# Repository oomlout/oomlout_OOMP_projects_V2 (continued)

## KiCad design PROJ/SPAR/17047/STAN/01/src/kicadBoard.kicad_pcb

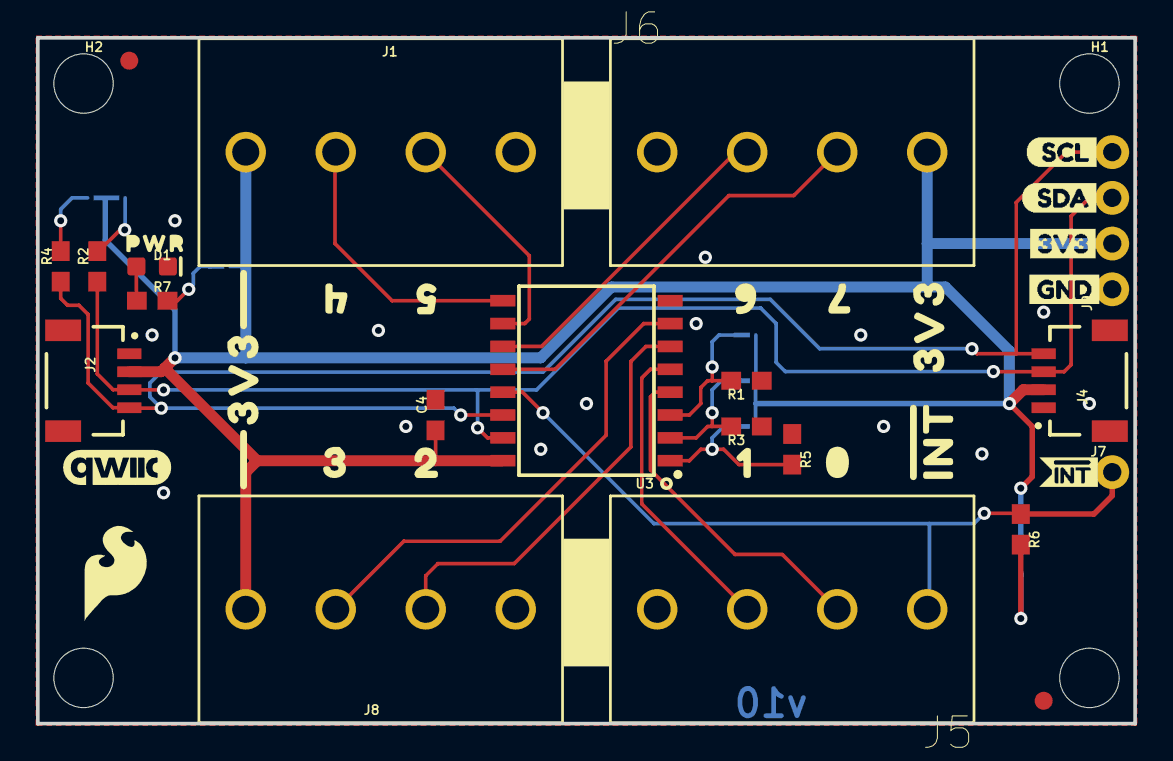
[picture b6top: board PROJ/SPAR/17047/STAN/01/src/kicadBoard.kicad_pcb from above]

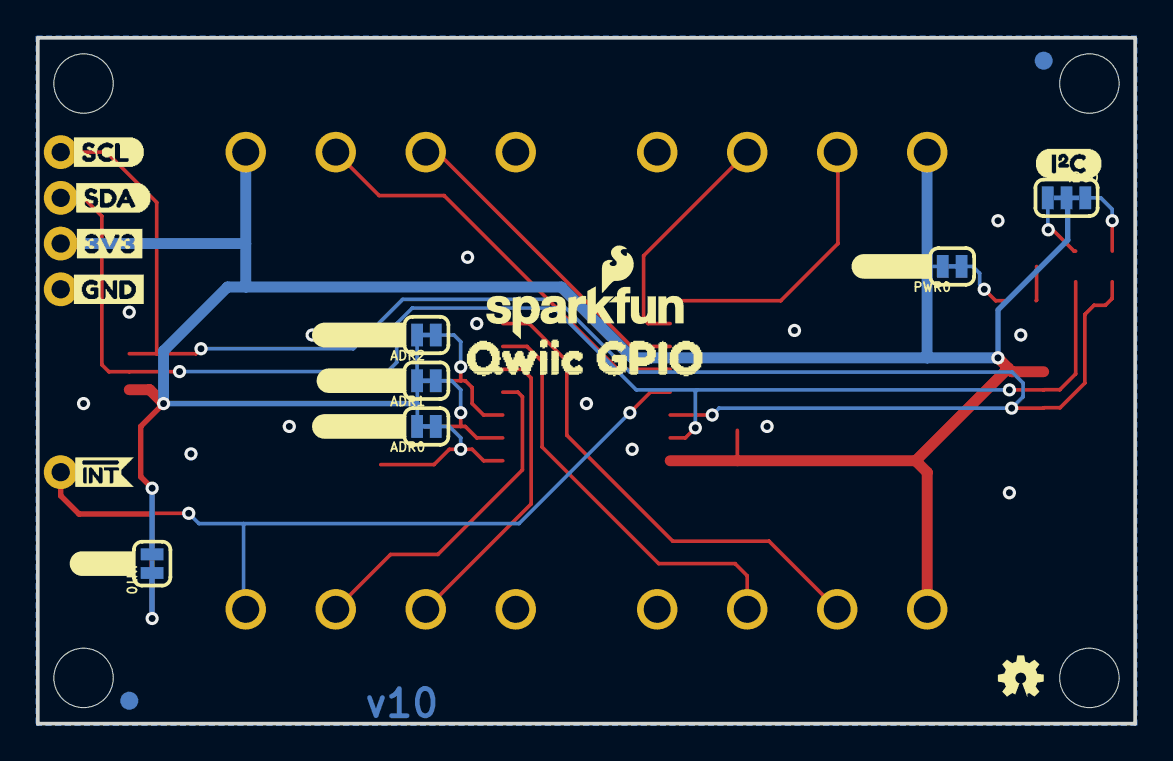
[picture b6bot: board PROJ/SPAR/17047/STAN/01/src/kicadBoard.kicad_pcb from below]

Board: 2 copper layers, 61.0 x 38.1 mm, 69 parts (22 on the bottom side), 21 nets.

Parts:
ADR0, ADR1, ADR2: JUMPER-SMT_2_NC_TRACE_SILK; SMT-JUMPER_2_NC_TRACE_SILK
C4: 0.1uF; 0603
D1: RED; LED-0603
FD1, FD2: FIDUCIAL1X2; FIDUCIAL-1X2
FRAME1: FRAME-LETTER; CREATIVE_COMMONS
H1, H2: STAND-OFF
I2C0: JUMPER-SMT_3_2-NC_TRACE_SILK; SMT-JUMPER_3_2-NC_TRACE_SILK
INT0: JUMPER-SMT_2_NC_TRACE_SILK; SMT-JUMPER_2_NC_TRACE_SILK
J1, J5, J6, J8: LATCHTERMINAL-5MM-4
J2, J4: QWIIC; JST04_1MM_RA
J7: 1X01_NO_SILK
J9: 1X04_NO_SILK
JP2, JP6: FIDUCIAL1X2; FIDUCIAL-1X2
JP3, JP4: STAND-OFF
LOGO1: OSHW-LOGOMINI; OSHW-LOGO-MINI
LOGO2: REVISION
LOGO3: SFE_LOGO_NAME_FLAME.1_INCH; SFE_LOGO_NAME_FLAME_.1
LOGO4: SFE_LOGO_FLAME.2_INCH; SFE_LOGO_FLAME_.2
PWR0: JUMPER-SMT_2_NC_TRACE_SILK; SMT-JUMPER_2_NC_TRACE_SILK
R1, R2, R3, R4, R5: 2.2k; 0603
R6: 10k; 0603
R7: 1k; 0603
U3: TCA9534; 16SOIC
U$1: I2C
U$2: 20
U$3, U$26: 3V33
U$4: 30
U$5: #ADR1#0
U$6: 10
U$7, U$25: GND4
U$8: QWIIC_GPIO7
U$9: SCL6
U$10: SDA5
U$11: #ADR2#0
U$12: #INT#0
U$13, U$22, U$29: #INT0
U$14: 00
U$15: #ADR0#0
U$21: QWIIC_6MM
U$23: SCL0
U$24: SDA1
U$30, U$31: 3V30
U$32: 40
U$33: 50
U$34: PWR0
U$35: 60
U$37: 70
U$38, U$40: #GND#0
U$39: #PWR#0

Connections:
3.3V: ADR0.2, ADR1.2, ADR2.2, C4.1, I2C0.2, INT0.2, J1.1, J2.2, J4.2, J6.4, J8.4, J9.2, PWR0.2, U3.16
ADR0: ADR0.1, R5.2, U3.1
ADR1: ADR1.1, R3.2, U3.2
ADR2: ADR2.1, R1.2, U3.3
GND: C4.2, D1.C, J1.4, J2.1, J4.1, J5.4, J6.1, J8.1, J9.1, R1.1, R3.1, R5.1, U3.8
unnamed: INT0.1, R6.2
unnamed: D1.A, R7.1
unnamed: PWR0.1, R7.2
P0: J5.2, U3.4
P1: J5.3, U3.5
P2: J8.2, U3.6
P3: J8.3, U3.7
P4: J1.2, U3.9
P5: J1.3, U3.10
P6: J6.2, U3.11
P7: J6.3, U3.12
SCL: J2.4, J4.4, J9.4, R4.1, U3.14
SCL_PU1: I2C0.1, R2.2
SDA: J2.3, J4.3, J9.3, R2.1, U3.15
SDA_PU1: I2C0.3, R4.2
~INT: J5.1, J7.1, R6.1, U3.13

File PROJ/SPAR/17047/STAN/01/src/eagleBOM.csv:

"Part";"Value";"Device";"Package";"Description";"DESIGNER";"PROD_ID";"REV";"STOREFRONT_SKU";"VALUE";
"ADR0";"JUMPER-SMT_2_NC_TRACE_SILK";"JUMPER-SMT_2_NC_TRACE_SILK";"SMT-JUMPER_2_NC_TRACE_SILK";"Normally closed trace jumper";"";"";"";"";"";
"ADR1";"JUMPER-SMT_2_NC_TRACE_SILK";"JUMPER-SMT_2_NC_TRACE_SILK";"SMT-JUMPER_2_NC_TRACE_SILK";"Normally closed trace jumper";"";"";"";"";"";
"ADR2";"JUMPER-SMT_2_NC_TRACE_SILK";"JUMPER-SMT_2_NC_TRACE_SILK";"SMT-JUMPER_2_NC_TRACE_SILK";"Normally closed trace jumper";"";"";"";"";"";
"C4";"0.1uF";"0.1UF-0603-25V-(+80/-20%)";"0603";"0.1µF ceramic capacitors";"";"CAP-00810";"";"";"0.1uF";
"D1";"RED";"LED-RED0603";"LED-0603";"Red SMD LED";"";"DIO-00819";"";"";"RED";
"FD1";"FIDUCIAL1X2";"FIDUCIAL1X2";"FIDUCIAL-1X2";"Fiducial Alignment Points";"";"";"";"";"";
"FD2";"FIDUCIAL1X2";"FIDUCIAL1X2";"FIDUCIAL-1X2";"Fiducial Alignment Points";"";"";"";"";"";
"FRAME1";"FRAME-LETTER";"FRAME-LETTER";"CREATIVE_COMMONS";"Schematic Frame - Letter";"";"";"";"";"";
"H1";"STAND-OFF";"STAND-OFF";"STAND-OFF";"Stand Off";"";"";"";"";"";
"H2";"STAND-OFF";"STAND-OFF";"STAND-OFF";"Stand Off";"";"";"";"";"";
"I2C";"JUMPER-SMT_3_2-NC_TRACE_SILK";"JUMPER-SMT_3_2-NC_TRACE_SILK";"SMT-JUMPER_3_2-NC_TRACE_SILK";"Normally closed trace jumper (2 of 2 connections)";"";"";"";"";"";
"INT";"JUMPER-SMT_2_NC_TRACE_SILK";"JUMPER-SMT_2_NC_TRACE_SILK";"SMT-JUMPER_2_NC_TRACE_SILK";"Normally closed trace jumper";"";"";"";"";"";
"J1";"";"CONN_04LATCH";"LATCHTERMINAL-5MM-4";"Multi connection point. Often used as Generic Header-pin footprint for 0.1 inch spaced/style header connections";"";"CON-14722";"";"PRT-15900";"";
"J2";"QWIIC";"QWIIC_CONNECTORJS-1MM";"JST04_1MM_RA";"SparkFun I2C Standard Qwiic Connector";"";"CONN-13694";"";"";"QWIIC_RIGHT_ANGLE";
"J4";"QWIIC";"QWIIC_CONNECTORJS-1MM";"JST04_1MM_RA";"SparkFun I2C Standard Qwiic Connector";"";"CONN-13694";"";"";"QWIIC_RIGHT_ANGLE";
"J5";"";"CONN_04LATCH";"LATCHTERMINAL-5MM-4";"Multi connection point. Often used as Generic Header-pin footprint for 0.1 inch spaced/style header connections";"";"CON-14722";"";"PRT-15900";"";
"J6";"";"CONN_04LATCH";"LATCHTERMINAL-5MM-4";"Multi connection point. Often used as Generic Header-pin footprint for 0.1 inch spaced/style header connections";"";"CON-14722";"";"PRT-15900";"";
"J7";"";"CONN_01PTH_NO_SILK_YES_STOP";"1X01_NO_SILK";"Single connection point. Often used as Generic Header-pin footprint for 0.1 inch spaced/style header connections";"";"";"";"";"";
"J8";"";"CONN_04LATCH";"LATCHTERMINAL-5MM-4";"Multi connection point. Often used as Generic Header-pin footprint for 0.1 inch spaced/style header connections";"";"CON-14722";"";"PRT-15900";"";
"J9";"";"CONN_041X04_NO_SILK";"1X04_NO_SILK";"Multi connection point. Often used as Generic Header-pin footprint for 0.1 inch spaced/style header connections";"";"CONN-09696";"";"";"";
"JP2";"FIDUCIAL1X2";"FIDUCIAL1X2";"FIDUCIAL-1X2";"Fiducial Alignment Points";"";"";"";"";"";
"JP3";"STAND-OFF";"STAND-OFF";"STAND-OFF";"Stand Off";"";"";"";"";"";
"JP4";"STAND-OFF";"STAND-OFF";"STAND-OFF";"Stand Off";"";"";"";"";"";
"JP6";"FIDUCIAL1X2";"FIDUCIAL1X2";"FIDUCIAL-1X2";"Fiducial Alignment Points";"";"";"";"";"";
"LOGO1";"OSHW-LOGOMINI";"OSHW-LOGOMINI";"OSHW-LOGO-MINI";"Open-Source Hardware (OSHW) Logo";"";"";"";"";"";
"LOGO2";"REVISION";"REVISION";"REVISION";""Revision By" Text";"";"";"";"";"";
"LOGO3";"SFE_LOGO_NAME_FLAME.1_INCH";"SFE_LOGO_NAME_FLAME.1_INCH";"SFE_LOGO_NAME_FLAME_.1";"SparkFun Font Logo w/ Flame";"";"";"";"";"";
"LOGO4";"SFE_LOGO_FLAME.2_INCH";"SFE_LOGO_FLAME.2_INCH";"SFE_LOGO_FLAME_.2";"SparkFun Flame Logo";"";"";"";"";"";
"PWR";"JUMPER-SMT_2_NC_TRACE_SILK";"JUMPER-SMT_2_NC_TRACE_SILK";"SMT-JUMPER_2_NC_TRACE_SILK";"Normally closed trace jumper";"";"";"";"";"";
"R1";"2.2k";"2.2KOHM-0603-1/10W-1%";"0603";"2.2kΩ resistor";"";"RES-08272";"";"";"2.2k";
"R2";"2.2k";"2.2KOHM-0603-1/10W-1%";"0603";"2.2kΩ resistor";"";"RES-08272";"";"";"2.2k";
"R3";"2.2k";"2.2KOHM-0603-1/10W-1%";"0603";"2.2kΩ resistor";"";"RES-08272";"";"";"2.2k";
"R4";"2.2k";"2.2KOHM-0603-1/10W-1%";"0603";"2.2kΩ resistor";"";"RES-08272";"";"";"2.2k";
"R5";"2.2k";"2.2KOHM-0603-1/10W-1%";"0603";"2.2kΩ resistor";"";"RES-08272";"";"";"2.2k";
"R6";"10k";"10KOHM-0603-1/10W-1%";"0603";"10kΩ resistor";"";"RES-00824";"";"";"10k";
"R7";"1k";"1KOHM-0603-1/10W-1%";"0603";"1kΩ resistor";"";"RES-07856";"";"";"1k";
"U3";"TCA9534";"TCA9534U";"16SOIC";"Texas Instruments TCA9534 I2C -> GPIO Expander";"";"IC-14889";"";"";"TCA9534";

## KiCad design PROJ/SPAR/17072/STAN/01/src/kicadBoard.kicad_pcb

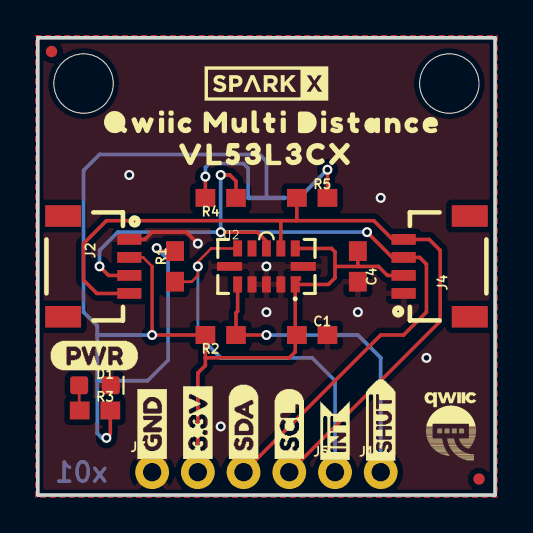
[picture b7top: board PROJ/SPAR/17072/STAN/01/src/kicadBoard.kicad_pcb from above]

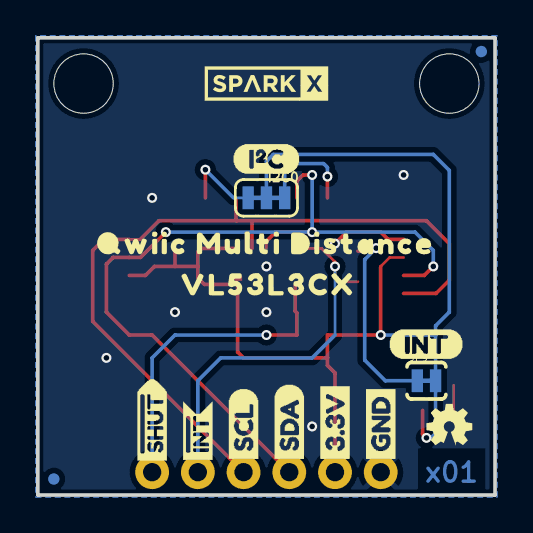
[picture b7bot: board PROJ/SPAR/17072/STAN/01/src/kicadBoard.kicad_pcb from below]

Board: 2 copper layers, 25.4 x 25.4 mm, 45 parts (16 on the bottom side), 10 nets.

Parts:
C1: 4.7uF; 0603
C4: 0.1uF; 0603
D1: RED; LED-0603
I2C0: SMT-JUMPER_3_2-NC_TRACE_SILK
J1, J5: 1X01_NO_SILK
J2, J4: 1X04_1MM_RA
J3: PTH; 1X04_NO_SILK
JP1, JP2, JP5, JP6: FIDUCIALUFIDUCIAL; MICRO-FIDUCIAL
JP3, JP4: STAND-OFF
JP9: INT; PAD-JUMPER-2-NC_BY_TRACE_YES_SILK
LOGO1: OSHW-LOGOMINI; OSHW-LOGO-MINI
R1, R2: 10k; 0603
R3: 1k; 0603
R4, R5: 2.2k; 0603
U2: VL53L3CX; VL53L1X
U$1, U$16: VL53L3CX0
U$2, U$15: QWIIC_MULTI_DISTANCE1
U$3, U$22: GND1
U$4, U$21: 3#3V2
U$5, U$27: SDA8
U$6, U$26: SCL9
U$7, U$14: INT#-[_
U$8, U$9: #SHUT15
U$10: (PWR)
U$11: (I_SUPER2_C)
U$12: (INT)
U$13: QWIIC-LOGO-SMALL
U$17, U$18: SPARKX-SMALL

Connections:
3.3V: C1.1, C4.1, I2C0.2, J2.2, J3.2, J4.2, JP9.2, R2.2, R3.2, U2.1, U2.11
GND: C1.2, C4.2, D1.C, J2.1, J3.1, J4.1, U2.2, U2.3, U2.4, U2.6, U2.12
unnamed: I2C0.1, R5.2
unnamed: I2C0.3, R4.2
unnamed: D1.A, R3.1
unnamed: JP9.1, R1.2
SCL: J2.4, J3.4, J4.4, R5.1, U2.10
SDA: J2.3, J3.3, J4.3, R4.1, U2.9
~INT: J5.1, R1.1, U2.7
~SHUT: J1.1, R2.1, U2.5

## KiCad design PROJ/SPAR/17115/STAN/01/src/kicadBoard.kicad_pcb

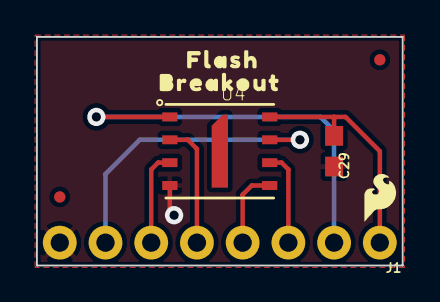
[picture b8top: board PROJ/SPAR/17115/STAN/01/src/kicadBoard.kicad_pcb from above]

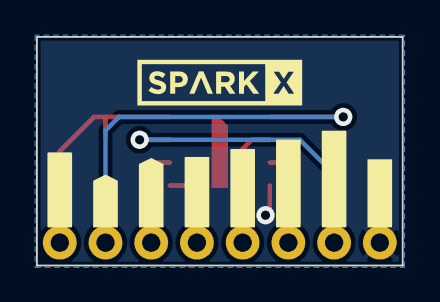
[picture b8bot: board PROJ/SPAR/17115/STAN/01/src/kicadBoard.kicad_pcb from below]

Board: 2 copper layers, 20.3 x 12.7 mm, 19 parts (9 on the bottom side), 8 nets.

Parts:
C29: 0.1uF; 0603
FD1, FD2: FIDUCIALUFIDUCIAL; FIDUCIAL-MICRO
FRAME2: FRAME-LETTER; CREATIVE_COMMONS
J1: 1X08_NO_SILK
LOGO2: OSHW-LOGONO_SILK; DUMMY
U4: W25QXX128MBIT-6X5; WSON-8-6X5-SKINNY_CENTERPAD
U$1: BREAKOUT1
U$2: FLASH0
U$3: SPARKX-LOGO4; SPARKX-MEDIUM
U$4: ##HLD##3#2
U$5: ##WP##2#3
U$6: SFE_LOGO_FLAME_.1
U$7: #3#3V#1
U$8: #CLK#6
U$9: #DI#0#5
U$10: #DO#1#4
U$11: #GND#0
U$12: ##CS##7

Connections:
3.3V: C29.1, J1.1, U4.8
GND: C29.2, J1.8, U4.4
QSPI0/DI: J1.4, U4.5
QSPI1/DO: J1.5, U4.2
QSPI2/~WP: J1.6, U4.3
QSPI3/~HOLD: J1.7, U4.7
QSPI-CLK: J1.3, U4.6
QSPI-~CS: J1.2, U4.1
